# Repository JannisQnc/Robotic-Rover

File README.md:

# Robotic-Rover
Its a Robotic Rover with IR sensors and an Ultrasonic sensor, so that it can follow lines and avoid obstacles.

It has an On/Off switch and 2 switches where you can enable and disable the 2 modes line following and obstacle avoidance.

I made it to get started with robotics and hardware but it can be fun to watch.

The step files are the parts I modelled myself for more complex parts I downloaded them on grabcad.

3D design:

Schematic:

PCB design:

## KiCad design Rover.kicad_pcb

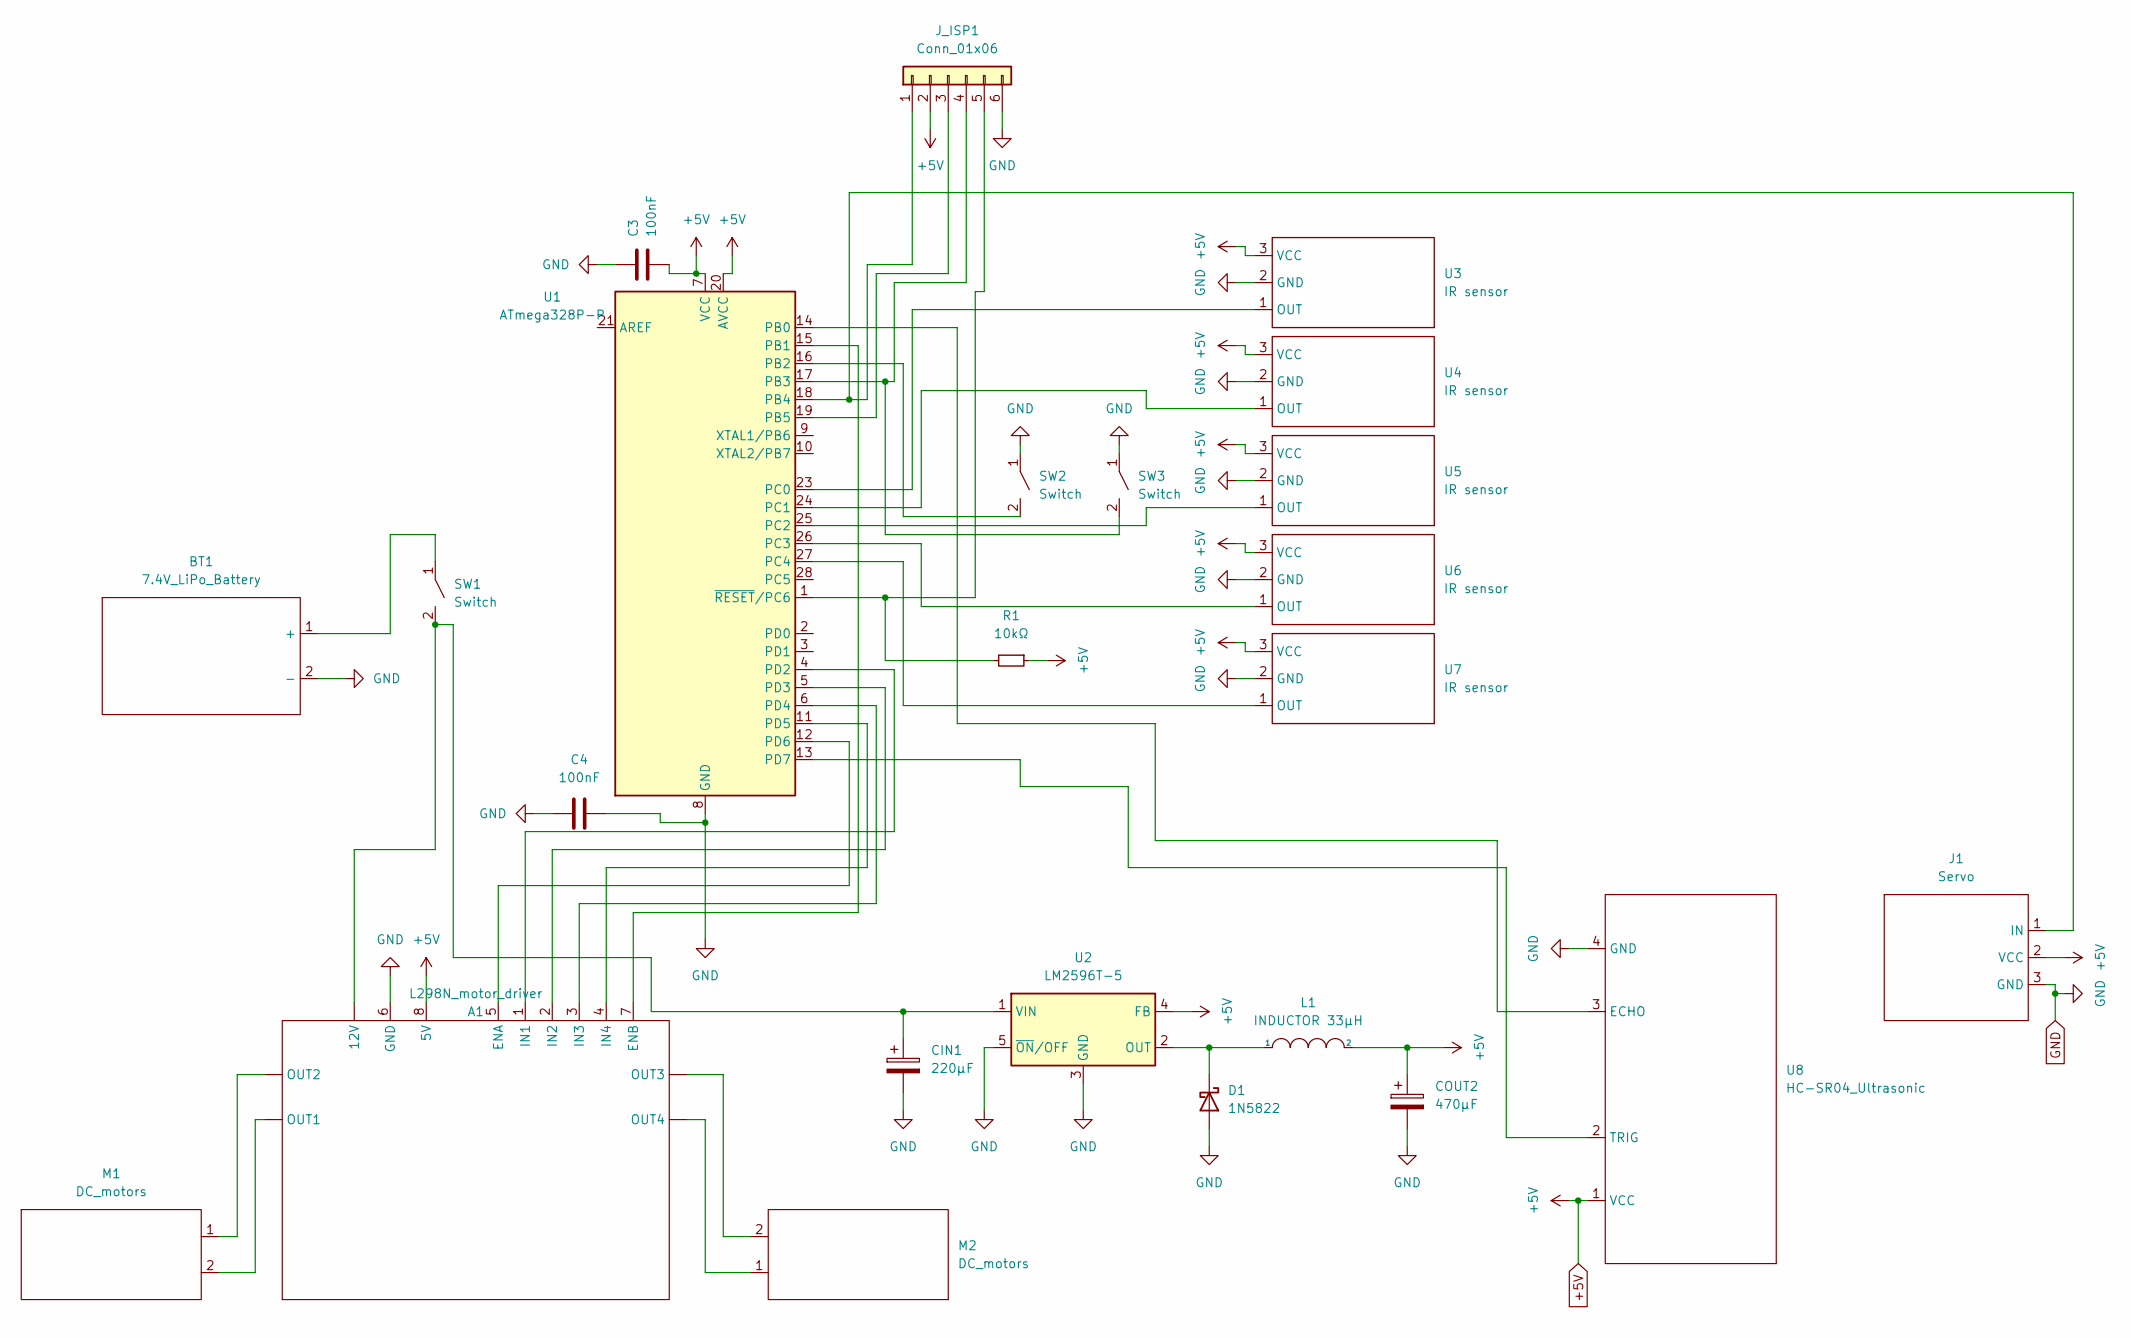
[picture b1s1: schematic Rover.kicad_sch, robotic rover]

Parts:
A1: L298N_motor_driver; PinHeader_1x08_P2.54mm_Vertical
BT1: 7.4V_LiPo_Battery; JST_EH_B2B-EH-A_1x02_P2.50mm_Vertical
C3, C4: 100nF; C_Radial_D4.0mm_H5.0mm_P1.50mm
CIN1: 220µF; C_Radial_D6.3mm_H11.0mm_P2.50mm
COUT2: 470µF; C_Radial_D6.3mm_H11.0mm_P2.50mm
D1: 1N5822; D_DO-201AD_P5.08mm_Vertical_KathodeUp
J1: Servo; PinHeader_1x03_P2.54mm_Vertical
J_ISP1: Conn_01x06; PinHeader_1x06_P2.54mm_Vertical
L1: INDUCTOR 33µH; L_Radial_L9.1mm_W9.1mm_Px6.35mm_Py6.35mm_Pulse_LP-25
M1, M2: DC_motors; PinHeader_1x02_P2.54mm_Vertical
R1: 10kΩ; R_Axial_DIN0207_L6.3mm_D2.5mm_P5.08mm_Vertical
SW1: Switch; PinHeader_1x02_P2.54mm_Vertical
SW2, SW3: Switch; PinHeader_1x03_P2.00mm_Vertical
U1: ATmega328P-P; DIP-28_W7.62mm
U2: LM2596T-5; TO-220-5_P3.4x3.7mm_StaggerOdd_Lead3.8mm_Vertical
U3, U4, U5, U6, U7: IR sensor; FanPinHeader_1x03_P2.54mm_Vertical
U8: HC-SR04_Ultrasonic; FanPinHeader_1x04_P2.54mm_Vertical

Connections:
+5V: A1.8 (5V), C3.2, COUT2.1, J1.2 (VCC), J_ISP1.2, L1.2, R1.1, U1.7 (VCC), U1.20 (AVCC), U2.4 (FB), U3.3 (VCC), U4.3 (VCC), U5.3 (VCC), U6.3 (VCC), U7.3 (VCC), U8.1 (VCC)
GND: A1.6 (GND), BT1.2 (-), C3.1, C4.1, C4.2, CIN1.2, COUT2.2, D1.2 (A), J1.3 (GND), J_ISP1.6, SW2.1, SW3.1, U1.8 (GND), U1.22 (GND), U2.3 (GND), U2.5 (~ON/OFF), U3.2 (GND), U4.2 (GND), U5.2 (GND), U6.2 (GND), U7.2 (GND), U8.4 (GND)
unnamed: A1.1 (IN1), U1.4 (PD2)
unnamed: A1.2 (IN2), U1.5 (PD3)
unnamed: A1.3 (IN3), U1.6 (PD4)
unnamed: A1.4 (IN4), U1.11 (PD5)
unnamed: A1.5 (ENA), U1.12 (PD6)
unnamed: A1.7 (ENB), U1.15 (PB1)
unnamed: A1. (12V), CIN1.1, M1.1, M1.2, M2.1, M2.2, SW1.2, U2.1 (VIN)
unnamed: BT1.1 (+), SW1.1
unnamed: D1.1 (K), L1.1, U2.2 (OUT)
unnamed: J1.1 (IN), J_ISP1.1, U1.18 (PB4)
unnamed: J_ISP1.3, U1.19 (PB5)
unnamed: J_ISP1.4, SW3.2, U1.17 (PB3)
unnamed: J_ISP1.5, R1.2, U1.1 (~RESET/PC6)
unnamed: SW2.2, U1.16 (PB2)
unnamed: U1.13 (PD7), U8.2 (TRIG)
unnamed: U1.14 (PB0), U8.3 (ECHO)
unnamed: U1.23 (PC0), U3.1 (OUT)
unnamed: U1.24 (PC1), U4.1 (OUT)
unnamed: U1.25 (PC2), U5.1 (OUT)
unnamed: U1.26 (PC3), U6.1 (OUT)
unnamed: U1.27 (PC4), U7.1 (OUT)

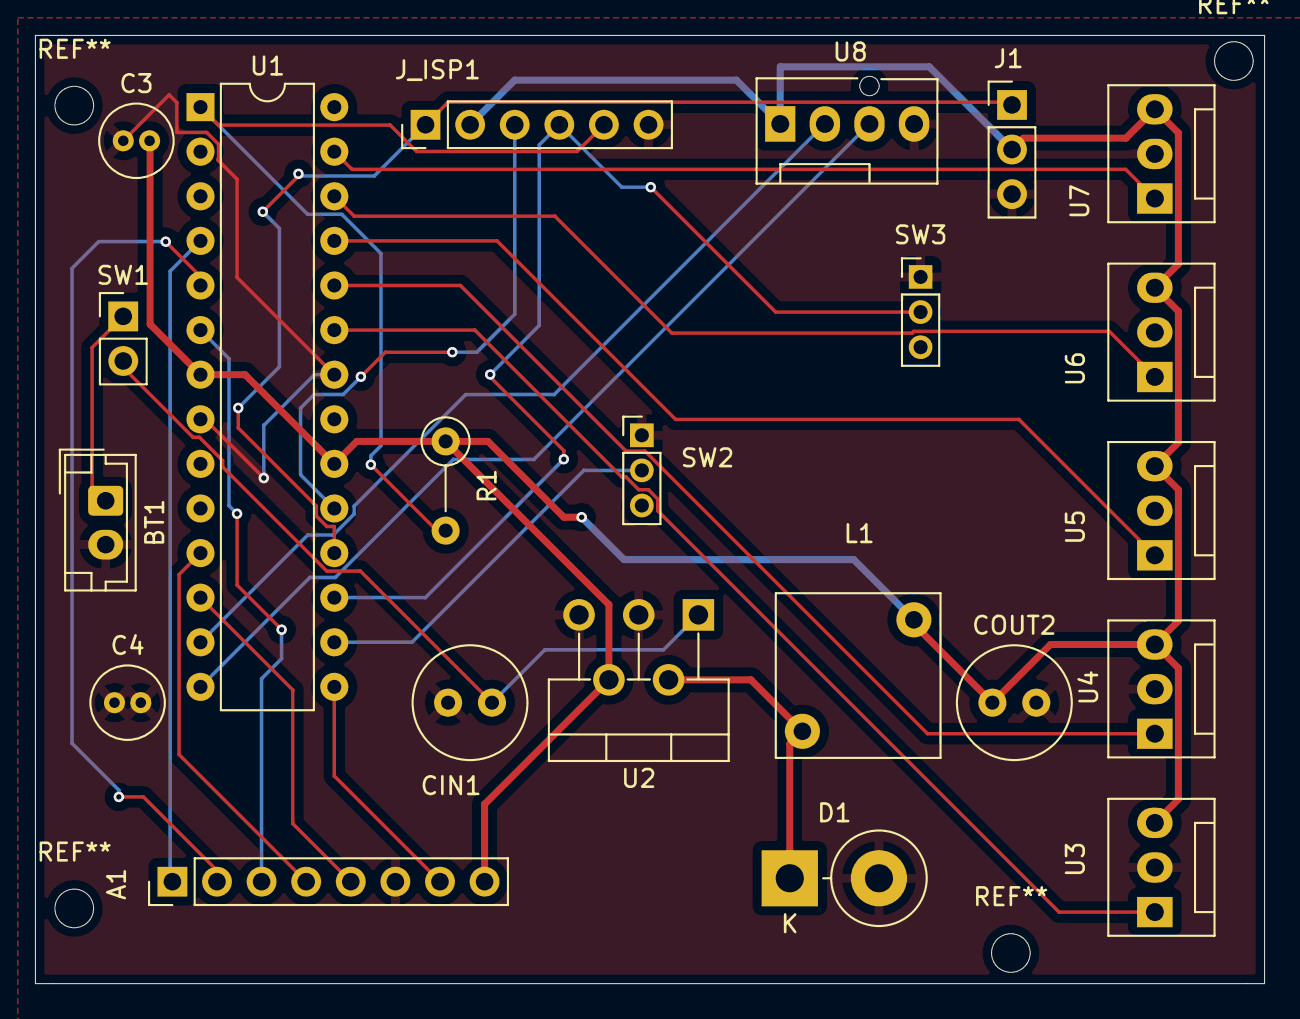
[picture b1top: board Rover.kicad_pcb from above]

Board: 2 copper layers, 70.0 x 54.0 mm, 22 parts (0 on the bottom side), 23 nets.

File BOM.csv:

"Component Count:" 25     
      
"Main Components:"      
  Value Quantity Price Link Note
  7.4V_LiPo_Battery 1 ?15.0 https://amzn.eu/d/02jSS1CU -
  100nF_capacitor 2 $1.64 https://www.digikey.com/short/tch2nrrh -
  220µF_capacitor 1 $0.32 https://www.digikey.com/short/mpwdc517 -
  470µF_capacitor 1 $0.34 https://www.digikey.com/short/rddp0m3c -
  1N5822_diode 1 $0.65 https://www.digikey.com/short/z3w8dzz5 -
  2_servo_motors 1 ?7.0 https://amzn.eu/d/02GwzsF5 "I could not find a single servo on Amazon"
  ISP_header 1 $0.33 https://www.digikey.com/short/3pq9j59h "To program the chip"
  Inductor_33µH 1 $1.74 https://www.digikey.com/short/p15jjj4h -
  10k?_resistor 1 $0.10 https://www.digikey.com/short/j9twzmr3 -
  Slide_switch 2 $1.44 https://www.digikey.com/short/mtv9j9z5 -
  Rocker_switch 1 $0.64 https://www.digikey.com/short/0427pm3w -
  LM2596T-5_regulator_switching 1 $5.67 https://www.digikey.com/short/7qzq8r15 -
  "IR sensor" 5 ?7.0 https://amzn.eu/d/0efVWsdq -
  "HC_SR04 Ultrasonic sensor" 1 ?2.5 https://amzn.eu/d/031g8wgf -
  "Acrylic chassis" 1 ?5.0 https://amzn.eu/d/0b8AxX8j -
  2_DC_motors_2_wheels_L298N_motor_driver_kit 1 ?11.0 https://amzn.eu/d/0iIssLBY "I know it's a kit but it contains only components I need"
  "4set_caster wheels" 1 ?6.5 https://amzn.eu/d/0fwzoVTM -
  ATmega328-PU_chip 1 $2.87 https://www.digikey.com/short/13bf5phz -
  PCB 1 $5.2 https://cart.jlcpcb.com/quote?quoteTab=standardPcb -
      
Tools:      
  Hot_glue_gun 1 ?6.6 https://amzn.eu/d/0cTl4LYC 
  M3_screws_nuts_standoffs_assortment 1 ?7.0 https://amzn.eu/d/02lEUhno 
  Needle_nose_plier 1 ?3.5 https://amzn.eu/d/0hGbAFfv 
  Digital_multimeter 1 ?11.3 https://amzn.eu/d/0hbpZf1F 
  Soldering_iron 1 ?20.0 https://amzn.eu/d/0eKS7nBW
